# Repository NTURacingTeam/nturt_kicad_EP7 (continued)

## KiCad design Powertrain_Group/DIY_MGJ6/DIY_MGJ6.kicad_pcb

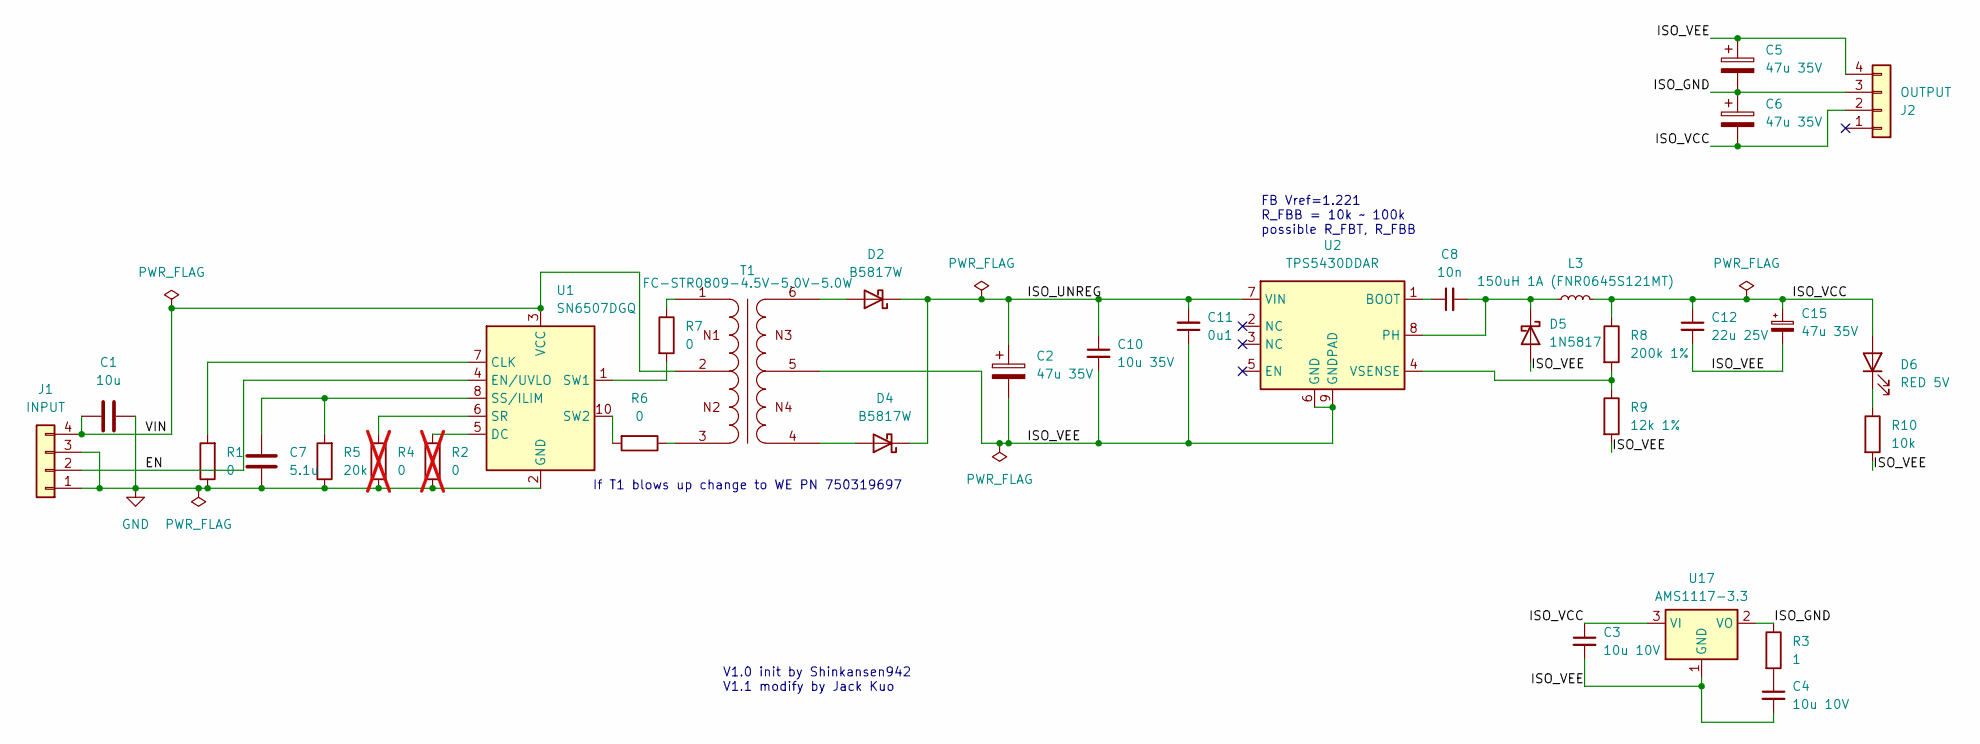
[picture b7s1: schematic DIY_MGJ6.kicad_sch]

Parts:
C1: 10u; C_1206_3216Metric
C2, C5, C6, C15: 47u 35V; CP_Elec_5x5.4
C3, C4: 10u 10V; C_1206_3216Metric
C7: 5.1u; C_0402_1005Metric
C8: 10n; C_0603_1608Metric
C10: 10u 35V; C_1206_3216Metric
C11: 0u1; C_0603_1608Metric
C12: 22u 25V; C_1206_3216Metric
D2, D4: B5817W; D_SOD-123
D5: 1N5817; D_SOD-123
D6: RED 5V; LED_0603_1608Metric
J1: INPUT; PinHeader_2x02_P2.54mm_Horizontal
J2: OUTPUT; PinHeader_2x02_P2.54mm_Horizontal
L3: 150uH 1A (FNR0645S121MT); L_APV_ANR6045
R1: 0; R_0402_1005Metric
R2, R4: 0; R_0402_1005Metric; not fitted
R3: 1; R_1206_3216Metric
R5: 20k; R_0402_1005Metric
R6, R7: 0; R_0805_2012Metric
R8: 200k 1%; R_0603_1608Metric
R9: 12k 1%; R_0603_1608Metric
R10: 10k; R_0603_1608Metric
T1: FC-STR0809-4.5V-5.0V-5.0W; T_Wurth_WE-PPTI-1308; Part Number 750319697
U1: SN6507DGQ; HVSSOP-10-1EP_3x3mm_P0.5mm_EP1.57x1.88mm
U2: TPS5430DDAR; TI_SO-PowerPAD-8_ThermalVias
U17: AMS1117-3.3; SOT-223-3_TabPin2

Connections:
/EN: J1.2, U1.4 (EN/UVLO)
/ISO_GND: C5.2, C6.1, J2.3, R3.1, U17.2 (VO)
/ISO_UNREG: C2.1, C10.1, C11.2, D2.1 (K), D4.1 (K), U2.7 (VIN)
/ISO_VCC: C3.1, C6.2, C12.1, C15.1, D6.2 (A), J2.2, L3.2, R8.1, U17.3 (VI)
/ISO_VEE: C2.2, C3.2, C4.2, C5.1, C10.2, C11.1, C12.2, C15.2, D5.2 (A), J2.4, R9.2, R10.2, T1.5, U2.6 (GND), U2.9 (GNDPAD), U17.1 (GND)
/VIN: C1.1, J1.4, T1.2, U1.3 (VCC)
GND: C1.2, C7.1, J1.1, J1.3, R1.1, R2.1, R4.1, R5.1, U1.2 (GND), U1.9 (GND), U1.11 (GND)
unnamed: C4.1, R3.2
unnamed: D2.2 (A), T1.6
unnamed: D4.2 (A), T1.4
unnamed: C8.2, D5.1 (K), L3.1, U2.8 (PH)
unnamed: D6.1 (K), R10.1
unnamed: R6.1, T1.3
unnamed: R7.1, T1.1
unnamed: R1.2, U1.7 (CLK)
unnamed: R2.2, U1.5 (DC)
unnamed: R4.2, U1.6 (SR)
unnamed: C7.2, R5.2, U1.8 (SS/ILIM)
unnamed: R7.2, U1.1 (SW1)
unnamed: R6.2, U1.10 (SW2)
unnamed: C8.1, U2.1 (BOOT)
unnamed: R8.2, R9.1, U2.4 (VSENSE)

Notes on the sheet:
FB Vref=1.221 R_FBB = 10k ~ 100k possible R_FBT, R_FBB
V1.0 init by Shinkansen942 V1.1 modify by Jack Kuo
If T1 blows up change to WE PN 750319697

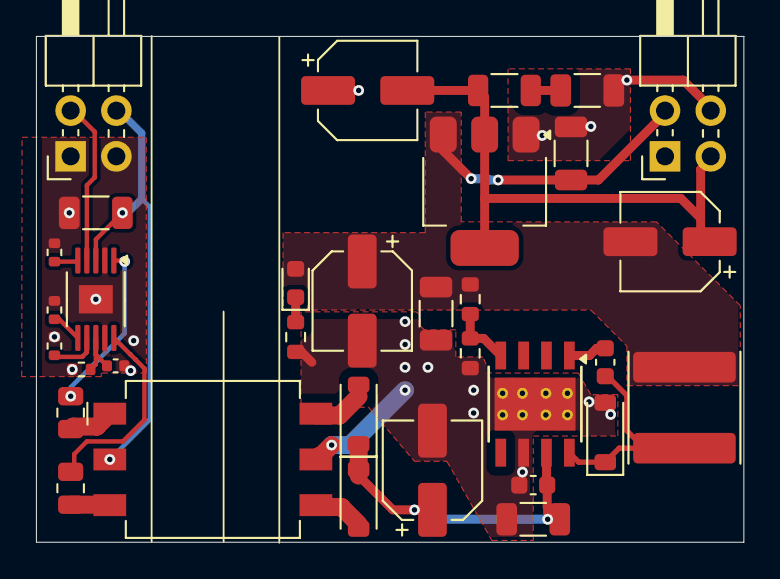
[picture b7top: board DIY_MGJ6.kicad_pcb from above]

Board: 2 copper layers, 39.3 x 28.1 mm, 33 parts (0 on the bottom side), 22 nets.

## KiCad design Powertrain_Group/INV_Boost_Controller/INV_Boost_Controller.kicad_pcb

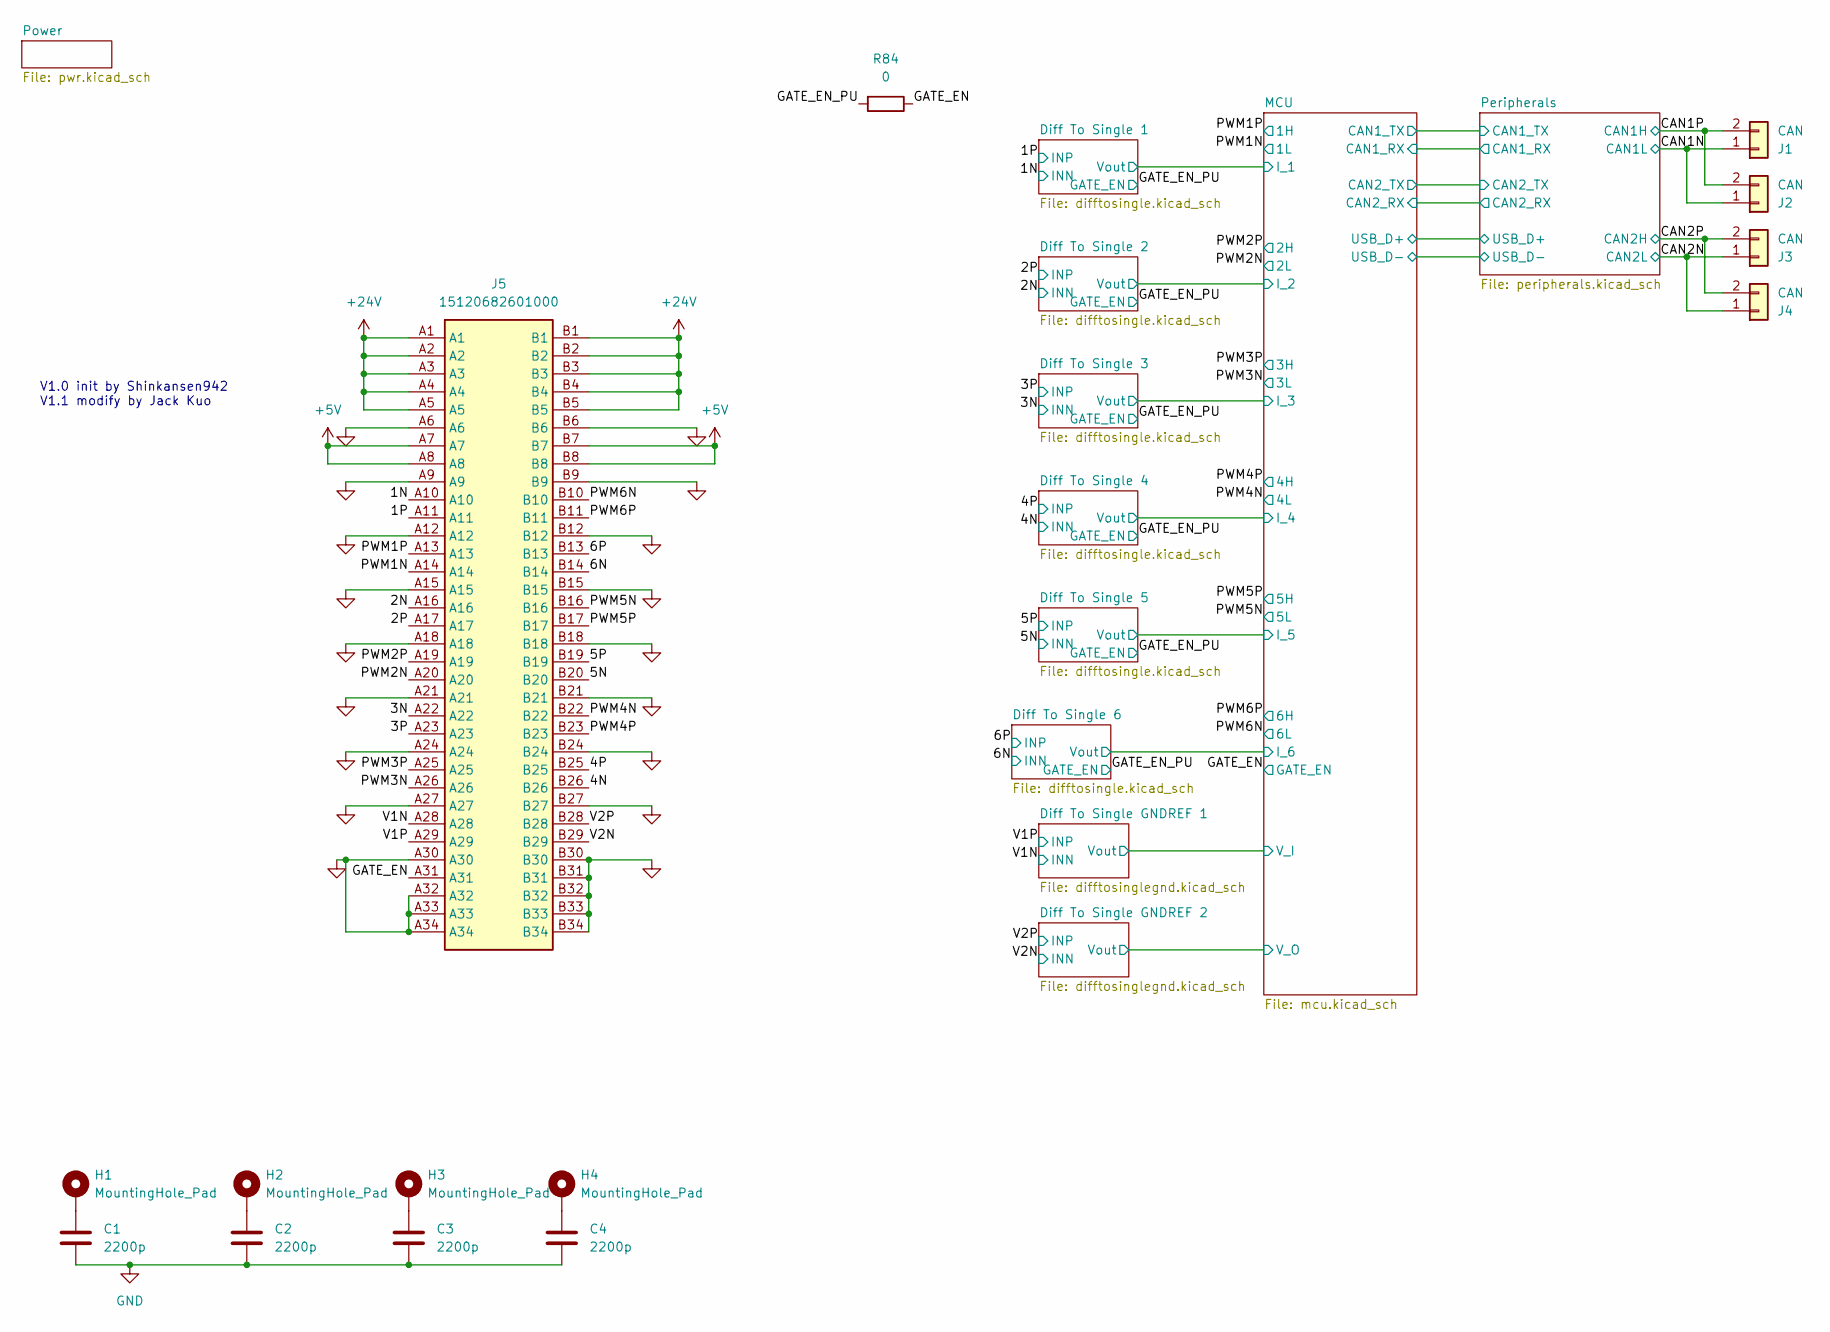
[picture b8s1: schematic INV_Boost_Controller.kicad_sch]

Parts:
C1, C2, C3, C4: 2200p; C_8060_Murata_DK1
H1, H2, H3, H4: MountingHole_Pad; MountingHole_4.3mm_M4_Pad_Via
J1, J2, J3, J4: CAN; JST_XH_B2B-XH-A_1x02_P2.50mm_Vertical
J5: 15120682601000; Harting 15120682601000; Manufacturer_Part_Number 15120682601000; Mouser Part Number 617-15120682601000
R84: 0; R_0402_1005Metric

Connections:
+5V: J5.A7, J5.A8, J5.B7, J5.B8; also elsewhere on the board
+24V: J5.A1, J5.A2, J5.A3, J5.A4, J5.A5, J5.B1, J5.B2, J5.B3, J5.B4, J5.B5; also elsewhere on the board
/1N: J5.A10; also elsewhere on the board
/1P: J5.A11; also elsewhere on the board
/2N: J5.A16; also elsewhere on the board
/2P: J5.A17; also elsewhere on the board
/3N: J5.A22; also elsewhere on the board
/3P: J5.A23; also elsewhere on the board
/4N: J5.B26; also elsewhere on the board
/4P: J5.B25; also elsewhere on the board
/5N: J5.B20; also elsewhere on the board
/5P: J5.B19; also elsewhere on the board
/6N: J5.B14; also elsewhere on the board
/6P: J5.B13; also elsewhere on the board
/CAN1N: J1.1, J2.1; also elsewhere on the board
/CAN1P: J1.2, J2.2; also elsewhere on the board
/CAN2N: J3.1, J4.1; also elsewhere on the board
/CAN2P: J3.2, J4.2; also elsewhere on the board
/GATE_EN: J5.A31, R84.1; also elsewhere on the board
/GATE_EN_PU: R84.2; also elsewhere on the board
/PWM1N: J5.A14; also elsewhere on the board
/PWM1P: J5.A13; also elsewhere on the board
/PWM2N: J5.A20; also elsewhere on the board
/PWM2P: J5.A19; also elsewhere on the board
/PWM3N: J5.A26; also elsewhere on the board
/PWM3P: J5.A25; also elsewhere on the board
/PWM4N: J5.B22; also elsewhere on the board
/PWM4P: J5.B23; also elsewhere on the board
/PWM5N: J5.B16; also elsewhere on the board
/PWM5P: J5.B17; also elsewhere on the board
/PWM6N: J5.B10; also elsewhere on the board
/PWM6P: J5.B11; also elsewhere on the board
/V1N: J5.A28; also elsewhere on the board
/V1P: J5.A29; also elsewhere on the board
/V2N: J5.B29; also elsewhere on the board
/V2P: J5.B28; also elsewhere on the board
GND: C1.1, C2.1, C3.1, C4.1, J5.A6, J5.A9, J5.A12, J5.A15, J5.A18, J5.A21, J5.A24, J5.A27, J5.A30, J5.A32, J5.A33, J5.A34, J5.B6, J5.B9, J5.B12, J5.B15, J5.B18, J5.B21, J5.B24, J5.B27, J5.B30, J5.B31, J5.B32, J5.B33, J5.B34; also elsewhere on the board
unnamed: C1.2, H1.1
unnamed: C2.2, H2.1
unnamed: C3.2, H3.1
unnamed: C4.2, H4.1

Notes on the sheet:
V1.0 init by Shinkansen942 V1.1 modify by Jack Kuo

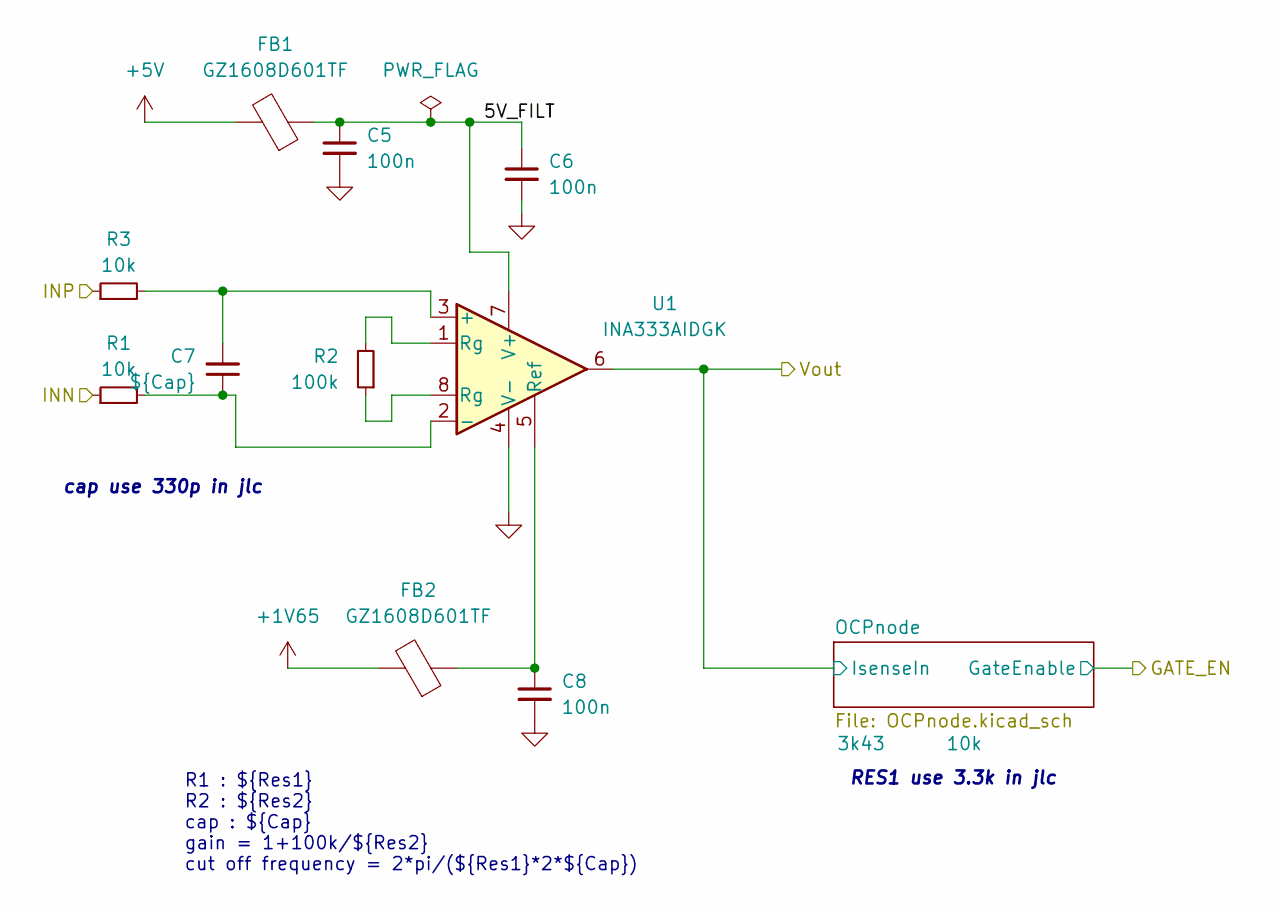
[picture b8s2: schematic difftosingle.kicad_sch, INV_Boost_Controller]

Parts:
C5, C6, C8: 100n; C_0402_1005Metric
C7: ${Cap}; C_0402_1005Metric
FB1, FB2: GZ1608D601TF; C_0603_1608Metric
R1, R3: 10k; R_0402_1005Metric
R2: 100k; R_0402_1005Metric
U1: INA333AIDGK; VSSOP-8_3x3mm_P0.65mm

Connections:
+1V65: FB2.2; also elsewhere on the board
+5V: FB1.2; also elsewhere on the board
/2N: R1.1; also elsewhere on the board
/2P: R3.1; also elsewhere on the board
/Diff To Single 2/5V_FILT: C5.1, C6.1, FB1.1, U1.7 (V+)
/Diff To Single 2/Vout: U1.6; also elsewhere on the board
GND: C5.2, C6.2, C8.2, U1.4 (V-); also elsewhere on the board
unnamed: R2.1, U1.8 (Rg)
unnamed: R2.2, U1.1 (Rg)
unnamed: C7.2, R3.2, U1.3 (+)
unnamed: C7.1, R1.2, U1.2 (-)
unnamed: C8.1, FB2.1, U1.5 (Ref)

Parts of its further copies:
C9, C10, C12, C13, C14, C16, C17, C18, C20, C21, C22, C24, C77, C78, C80: 100n; C_0402_1005Metric
FB3, FB4, FB5, FB6, FB7, FB8, FB9, FB10, FB16, FB17: GZ1608D601TF; C_0603_1608Metric
R4, R6, R7, R9, R10, R12, R13, R15, R62, R64: 10k; R_0402_1005Metric
R5, R8, R11, R14, R63: 100k; R_0402_1005Metric
U2, U3, U4, U5, U16: INA333AIDGK; VSSOP-8_3x3mm_P0.65mm

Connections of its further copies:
+1V65: FB4.2, FB6.2, FB8.2, FB10.2, FB17.2; also elsewhere on the board
+5V: FB3.2, FB5.2, FB7.2, FB9.2, FB16.2; also elsewhere on the board
/1N: R62.1; also elsewhere on the board
/1P: R64.1; also elsewhere on the board
/3N: R4.1; also elsewhere on the board
/3P: R6.1; also elsewhere on the board
/4N: R7.1; also elsewhere on the board
/4P: R9.1; also elsewhere on the board
/5N: R10.1; also elsewhere on the board
/5P: R12.1; also elsewhere on the board
/6N: R13.1; also elsewhere on the board
/6P: R15.1; also elsewhere on the board
/Diff To Single 1/5V_FILT: C77.1, C78.1, FB16.1, U16.7 (V+)
/Diff To Single 1/Vout: U16.6; also elsewhere on the board
/Diff To Single 3/5V_FILT: C9.1, C10.1, FB3.1, U2.7 (V+)
/Diff To Single 3/Vout: U2.6; also elsewhere on the board
/Diff To Single 4/5V_FILT: C13.1, C14.1, FB5.1, U3.7 (V+)
/Diff To Single 4/Vout: U3.6; also elsewhere on the board
/Diff To Single 5/5V_FILT: C17.1, C18.1, FB7.1, U4.7 (V+)
/Diff To Single 5/Vout: U4.6; also elsewhere on the board
/Diff To Single 6/5V_FILT: C21.1, C22.1, FB9.1, U5.7 (V+)
/Diff To Single 6/Vout: U5.6; also elsewhere on the board
GND: C9.2, C10.2, C12.2, C13.2, C14.2, C16.2, C17.2, C18.2, C20.2, C21.2, C22.2, C24.2, C77.2, C78.2, C80.2, U2.4 (V-), U3.4 (V-), U4.4 (V-), U5.4 (V-), U16.4 (V-); also elsewhere on the board
unnamed: R5.1, U2.8 (Rg)
unnamed: R5.2, U2.1 (Rg)
unnamed: R8.1, U3.8 (Rg)
unnamed: R8.2, U3.1 (Rg)
unnamed: R11.1, U4.8 (Rg)
unnamed: R11.2, U4.1 (Rg)
unnamed: R14.1, U5.8 (Rg)
unnamed: R14.2, U5.1 (Rg)
unnamed: R63.1, U16.8 (Rg)
unnamed: R63.2, U16.1 (Rg)
unnamed 143: R6.2, U2.3 (+); also elsewhere on the board
unnamed 144: R4.2, U2.2 (-); also elsewhere on the board
unnamed: C12.1, FB4.1, U2.5 (Ref)
unnamed 146: R9.2, U3.3 (+); also elsewhere on the board
unnamed 147: R7.2, U3.2 (-); also elsewhere on the board
unnamed: C16.1, FB6.1, U3.5 (Ref)
unnamed 149: R12.2, U4.3 (+); also elsewhere on the board
unnamed 150: R10.2, U4.2 (-); also elsewhere on the board
unnamed: C20.1, FB8.1, U4.5 (Ref)
unnamed 152: R15.2, U5.3 (+); also elsewhere on the board
unnamed 153: R13.2, U5.2 (-); also elsewhere on the board
unnamed: C24.1, FB10.1, U5.5 (Ref)
unnamed 170: R64.2, U16.3 (+); also elsewhere on the board
unnamed 171: R62.2, U16.2 (-); also elsewhere on the board
unnamed: C80.1, FB17.1, U16.5 (Ref)

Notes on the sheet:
R1 : ${Res1} R2 : ${Res2} cap : ${Cap} gain = 1+100k/${Res2} cut off frequency = 2*pi/(${Res1}*2*${Cap})
cap use 330p in jlc
RES1 use 3.3k in jlc

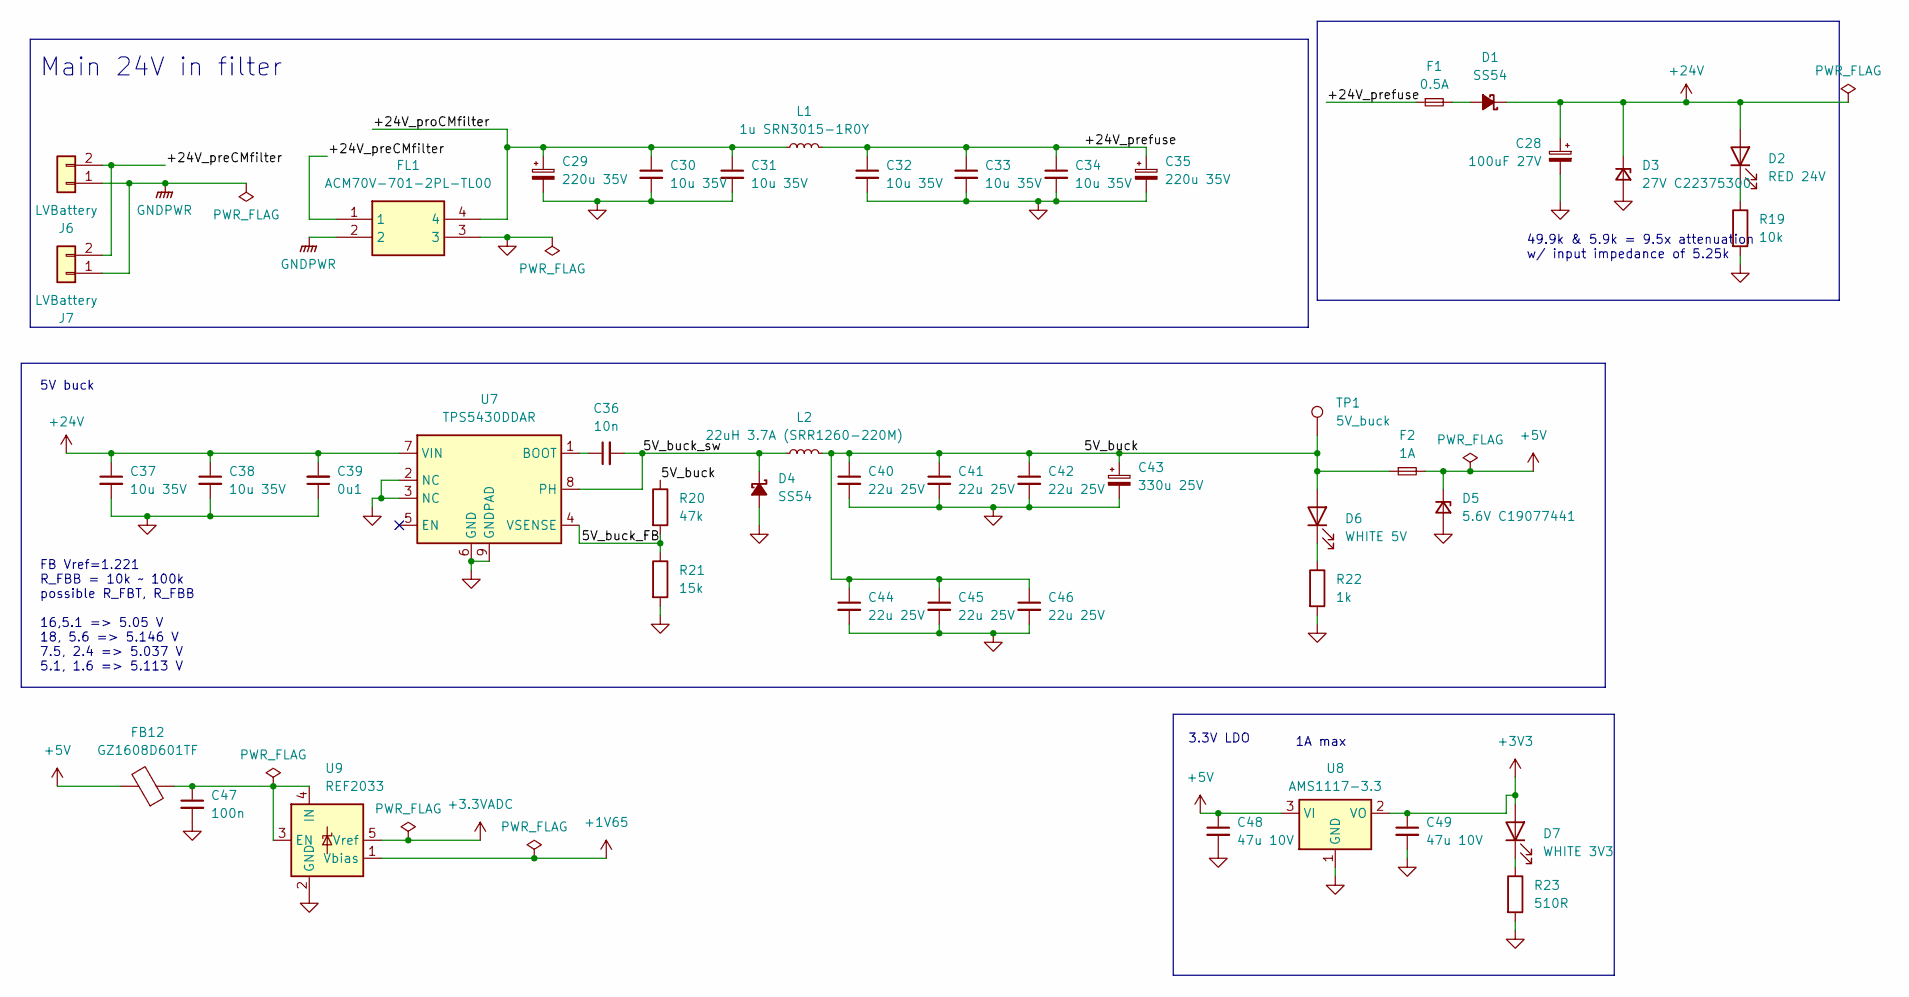
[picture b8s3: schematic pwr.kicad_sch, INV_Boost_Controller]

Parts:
C28: 100uF 27V; CP_Radial_D10.0mm_P5.00mm
C29, C35: 220u 35V; CP_Radial_D8.0mm_P3.80mm
C30, C31, C32, C33, C34, C37, C38: 10u 35V; C_1206_3216Metric
C36: 10n; C_0603_1608Metric
C39: 0u1; C_0603_1608Metric
C40, C41, C42, C44, C45, C46: 22u 25V; C_1206_3216Metric
C43: 330u 25V; CP_Radial_D8.0mm_P3.80mm
C47: 100n; C_0402_1005Metric
C48, C49: 47u 10V; C_1206_3216Metric
D1, D4: SS54; D_SMA
D2: RED 24V; LED_0603_1608Metric
D3: 27V C22375300; D_SOD-323
D5: 5.6V C19077441; D_SOD-323
D6: WHITE 5V; LED_0603_1608Metric
D7: WHITE 3V3; LED_0603_1608Metric
F1: 0.5A; Fuse_1206_3216Metric
F2: 1A; Fuse_1206_3216Metric
FB12: GZ1608D601TF; C_0603_1608Metric
FL1: ACM70V-701-2PL-TL00; Common_Mode_Choke_4A_ACM70V7012PLTL00; Mouser Part Number 810-ACM70V7012PLTL00
J6, J7: LVBattery; JST_VH_B2P-VH_1x02_P3.96mm_Vertical
L1: 1u SRN3015-1R0Y; L_Wuerth_MAPI-3015
L2: 22uH 3.7A (SRR1260-220M); L_Bourns_SRR1260
R19: 10k; R_0402_1005Metric
R20: 47k; R_0603_1608Metric
R21: 15k; R_0603_1608Metric
R22: 1k; R_0402_1005Metric
R23: 510R; R_0402_1005Metric
TP1: 5V_buck; TestPoint_Pad_D1.0mm
U7: TPS5430DDAR; TI_SO-PowerPAD-8_ThermalVias
U8: AMS1117-3.3; SOT-223-3_TabPin2
U9: REF2033; SOT-23-5

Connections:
+1V65: U9.1 (Vbias); also elsewhere on the board
+3.3VADC: U9.5 (Vref); also elsewhere on the board
+3V3: C49.1, D7.2 (A), U8.2 (VO); also elsewhere on the board
+5V: C48.1, D5.1 (K), F2.2, FB12.2, U8.3 (VI); also elsewhere on the board
+24V: C28.1, C37.1, C38.1, C39.2, D1.1 (K), D2.2 (A), D3.1 (K), U7.7 (VIN); also elsewhere on the board
/Power/5V_buck: C40.1, C41.1, C42.1, C43.1, C44.1, C45.1, C46.1, D6.2 (A), F2.1, L2.2, R20.1, TP1.1
/Power/5V_buck_FB: R20.2, R21.1, U7.4 (VSENSE)
/Power/5V_buck_sw: C36.2, D4.1 (K), L2.1, U7.8 (PH)
/Power/+24V_preCMfilter: FL1.1, J6.2, J7.2
/Power/+24V_prefuse: C32.1, C33.1, C34.1, C35.1, F1.1, L1.2
/Power/+24V_proCMfilter: C29.1, C30.1, C31.1, FL1.4, L1.1
GND: C28.2, C29.2, C30.2, C31.2, C32.2, C33.2, C34.2, C35.2, C37.2, C38.2, C39.1, C40.2, C41.2, C42.2, C43.2, C44.2, C45.2, C46.2, C47.2, C48.2, C49.2, D3.2 (A), D4.2 (A), D5.2 (A), FL1.3, R19.2, R21.2, R22.2, R23.2, U7.2 (NC), U7.3 (NC), U7.6 (GND), U7.9 (GNDPAD), U8.1 (GND), U9.2 (GND); also elsewhere on the board
GNDPWR: FL1.2, J6.1, J7.1
unnamed: D1.2 (A), F1.2
unnamed: D2.1 (K), R19.1
unnamed: D6.1 (K), R22.1
unnamed: D7.1 (K), R23.1
unnamed: C36.1, U7.1 (BOOT)
unnamed: C47.1, FB12.1, U9.3 (EN), U9.4 (IN)

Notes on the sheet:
1A max
FB Vref=1.221 R_FBB = 10k ~ 100k possible R_FBT, R_FBB 16,5.1 => 5.05 V 18, 5.6 => 5.146 V 7.5, 2.4 => 5.037 V 5.1, 1.6 => 5.113 V
Main 24V in filter
49.9k & 5.9k = 9.5x attenuation w/ input impedance of 5.25k
5V buck
3.3V LDO

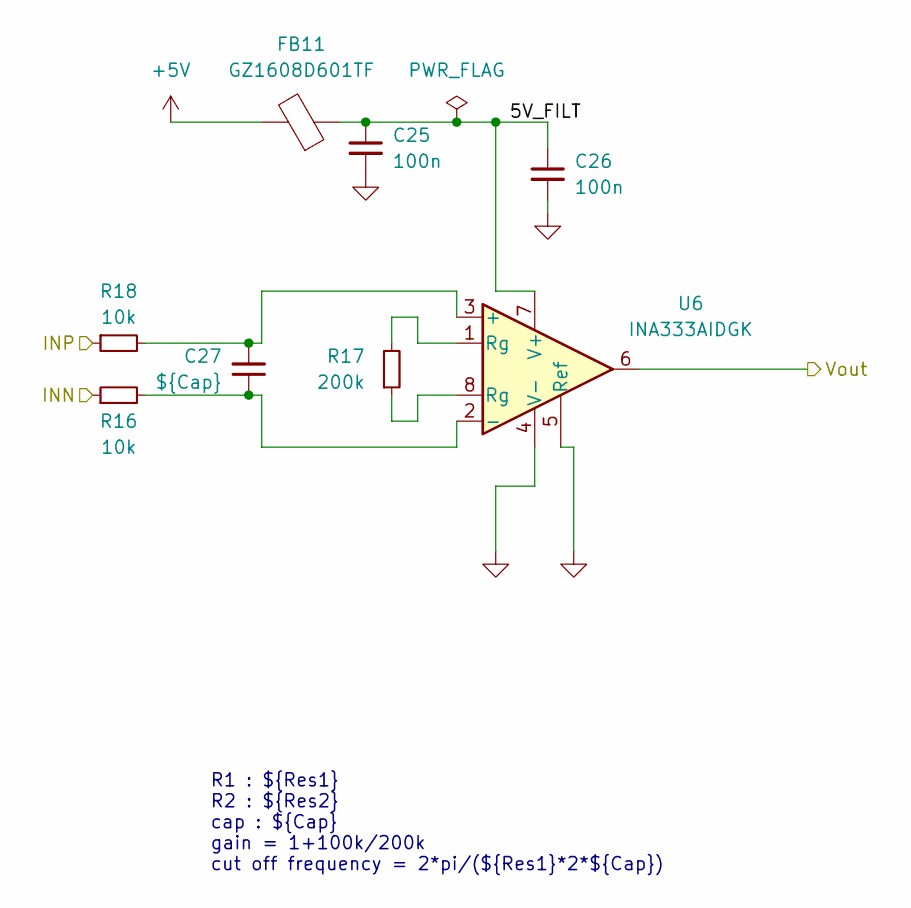
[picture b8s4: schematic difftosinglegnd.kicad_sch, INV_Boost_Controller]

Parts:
C25, C26: 100n; C_0402_1005Metric
C27: ${Cap}; C_0402_1005Metric
FB11: GZ1608D601TF; C_0603_1608Metric
R16, R18: 10k; R_0402_1005Metric
R17: 200k; R_0402_1005Metric
U6: INA333AIDGK; VSSOP-8_3x3mm_P0.65mm

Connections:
+5V: FB11.2; also elsewhere on the board
/Diff To Single GNDREF 1/5V_FILT: C25.1, C26.1, FB11.1, U6.7 (V+)
/Diff To Single GNDREF 1/Vout: U6.6; also elsewhere on the board
/V1N: R16.1; also elsewhere on the board
/V1P: R18.1; also elsewhere on the board
GND: C25.2, C26.2, U6.4 (V-), U6.5 (Ref); also elsewhere on the board
unnamed: R17.1, U6.8 (Rg)
unnamed: R17.2, U6.1 (Rg)
unnamed: C27.2, R18.2, U6.3 (+)
unnamed: C27.1, R16.2, U6.2 (-)

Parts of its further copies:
C81, C82: 100n; C_0402_1005Metric
FB18: GZ1608D601TF; C_0603_1608Metric
R65, R67: 10k; R_0402_1005Metric
R66: 200k; R_0402_1005Metric
U17: INA333AIDGK; VSSOP-8_3x3mm_P0.65mm

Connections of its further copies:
+5V: FB18.2; also elsewhere on the board
/Diff To Single GNDREF 2/5V_FILT: C81.1, C82.1, FB18.1, U17.7 (V+)
/Diff To Single GNDREF 2/Vout: U17.6; also elsewhere on the board
/V2N: R65.1; also elsewhere on the board
/V2P: R67.1; also elsewhere on the board
GND: C81.2, C82.2, U17.4 (V-), U17.5 (Ref); also elsewhere on the board
unnamed: R66.1, U17.8 (Rg)
unnamed: R66.2, U17.1 (Rg)
unnamed 173: R67.2, U17.3 (+); also elsewhere on the board
unnamed 174: R65.2, U17.2 (-); also elsewhere on the board

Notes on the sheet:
R1 : ${Res1} R2 : ${Res2} cap : ${Cap} gain = 1+100k/200k cut off frequency = 2*pi/(${Res1}*2*${Cap})

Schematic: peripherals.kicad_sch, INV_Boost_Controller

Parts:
C50, C55: 4u7 10v; C_0402_1005Metric
C51, C52, C56, C57: 0u1; C_0402_1005Metric
C53, C54, C58, C59: 22p; C_0402_1005Metric
D8, D9: NUP2105L; SOT-23
FL2, FL3: EXC-X4CE900U; EXCX4CE900U; Mouser Part Number 667-EXC-X4CE900U
J8: USB_C_Receptacle_USB2.0_16P; USB_C_Receptacle_G-Switch_GT-USB-7051x
R24, R25, R28, R29: 22R; R_0402_1005Metric
R26, R30: 90R; R_0402_1005Metric; not fitted
R27, R31: 10k; R_0402_1005Metric
R32, R33: 5.1k; R_0402_1005Metric
SW1: SW_DIP_x01; SW_DIP_SPSTx01_Slide_9.78x4.72mm_W7.62mm_P2.54mm
U10, U11: TCAN1042VDRQ1; SOIC-8_3.9x4.9mm_P1.27mm
U12: SRV05-4; SOT-23-6

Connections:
+3V3: C52.1, C57.1, U10.5 (VIO), U11.5 (VIO); also elsewhere on the board
+5V: C50.1, C51.1, C55.1, C56.1, SW1.1, U10.3 (VCC), U11.3 (VCC); also elsewhere on the board
/CAN1N: C58.1, D9.1 (K), FL3.3, R30.2; also elsewhere on the board
/CAN1P: C59.1, D9.2 (K), FL3.4, R30.1; also elsewhere on the board
/CAN2N: C53.1, D8.1 (K), FL2.3, R26.2; also elsewhere on the board
/CAN2P: C54.1, D8.2 (K), FL2.4, R26.1; also elsewhere on the board
/MCU/CAN1_RX: R29.1; also elsewhere on the board
/MCU/CAN1_TX: R28.1; also elsewhere on the board
/MCU/CAN2_RX: R25.1; also elsewhere on the board
/MCU/CAN2_TX: R24.1; also elsewhere on the board
/Peripherals/D+: J8.A6 (D+), J8.B6 (D+), U12.3 (IO2), U12.4 (IO3); also elsewhere on the board
/Peripherals/D-: J8.A7 (D-), J8.B7 (D-), U12.1 (IO1), U12.6 (IO4); also elsewhere on the board
/Peripherals/PRE_CAN1N: FL3.2, U11.6 (CANL)
/Peripherals/PRE_CAN1P: FL3.1, U11.7 (CANH)
/Peripherals/PRE_CAN2N: FL2.2, U10.6 (CANL)
/Peripherals/PRE_CAN2P: FL2.1, U10.7 (CANH)
/Peripherals/VBUS: J8.A4 (VBUS), J8.A9 (VBUS), J8.B4 (VBUS), J8.B9 (VBUS), SW1.2, U12.5 (VP)
GND: C50.2, C51.2, C52.2, C53.2, C54.2, C55.2, C56.2, C57.2, C58.2, C59.2, D8.3 (A), D9.3 (A), J8.A1 (GND), J8.A12 (GND), J8.B1 (GND), J8.B12 (GND), J8.S1 (SHIELD), R27.2, R31.2, R32.2, R33.2, U10.2 (GND), U11.2 (GND), U12.2 (VN); also elsewhere on the board
unnamed: J8.A5 (CC1), R32.1
unnamed: J8.B5 (CC2), R33.1
unnamed: R25.2, U10.4 (RXD)
unnamed: R27.1, U10.8 (STB)
unnamed: R24.2, U10.1 (TXD)
unnamed: R29.2, U11.4 (RXD)
unnamed: R31.1, U11.8 (STB)
unnamed: R28.2, U11.1 (TXD)

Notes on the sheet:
CAN1
cap reference: https://www.nxp.com/docs/en/supporting-information/AH1014_v1_4_Application_Hints_TJA1042_43_48_51.pdf
CAN2
we use 1M => about 50pF to ground for both H and L but 30pF already persist in NUP2105 => only 22pF added additionaly but additionaly, TCAN1042 itself has 24pF to GND and 12pF H to L.
USB

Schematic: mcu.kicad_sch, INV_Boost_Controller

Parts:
C60, C61, C62, C63, C64: 100n; C_0402_1005Metric
C65, C66: 4u7; C_0402_1005Metric
C67, C70, C71, C73: 0u1; C_0402_1005Metric
C68, C69: 10u 6V; C_0402_1005Metric
C72, C74: 27p; C_0402_1005Metric
D10, D14: R LED; LED_0603_1608Metric
D11, D15: Y LED; LED_0603_1608Metric
D12, D16: G LED; LED_0603_1608Metric
D13, D17: B LED; LED_0603_1608Metric
FB13: GZ1608D601TF; C_0603_1608Metric
J9: STDC14; box_header_14P_pitch1.27
J10, J11, J12, J13: TEMP; JST_XA_B02B-XASK-1_1x02_P2.50mm_Vertical
J14: MSD-4-A; MSD4A; Mouser Part Number 179-MSD-4-A
R34, R35, R36, R37, R38, R39, R40: 10k; R_0402_1005Metric
R41: 100R; R_0402_1005Metric
R42, R43, R44, R45, R46, R47, R48, R49: 2k2; R_0402_1005Metric
R50, R51, R52, R53: 4k7; R_0402_1005Metric
SW2, SW3: TS-1187A-B-A-B; SW_SPST_TL3342
U13: STM32G474VETx; LQFP-100_14x14mm_P0.5mm
Y1: X322516MLB4SI (16MHz); Crystal_SMD_3225-4Pin_3.2x2.5mm

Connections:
+3.3VADC: C69.1, FB13.2, R36.1, R37.1, R38.1, R39.1; also elsewhere on the board
+3V3: C60.1, C61.1, C62.1, C63.1, C64.1, C65.1, C66.1, J9.3, J14.4 (VDD), R34.1, R50.2, R51.2, R52.2, R53.2, SW3.1, U13.6 (VBAT), U13.24 (VDD), U13.49 (VDD), U13.64 (VDD), U13.75 (VDD), U13.100 (VDD); also elsewhere on the board
/Diff To Single 1/Vout: U13.21 (PA1); also elsewhere on the board
/Diff To Single 2/Vout: U13.22 (PA2); also elsewhere on the board
/Diff To Single 3/Vout: U13.25 (PA3); also elsewhere on the board
/Diff To Single 4/Vout: U13.26 (PA4); also elsewhere on the board
/Diff To Single 5/Vout: U13.27 (PA5); also elsewhere on the board
/Diff To Single 6/Vout: U13.28 (PA6); also elsewhere on the board
/Diff To Single GNDREF 1/Vout: U13.32 (PB0); also elsewhere on the board
/Diff To Single GNDREF 2/Vout: U13.33 (PB1); also elsewhere on the board
/GATE_EN: R40.2; also elsewhere on the board
/MCU/BOOT0: C73.1, R35.2, SW3.2, U13.95 (PB8)
/MCU/CAN1_RX: U13.82 (PD0); also elsewhere on the board
/MCU/CAN1_TX: U13.83 (PD1); also elsewhere on the board
/MCU/CAN2_RX: U13.92 (PB5); also elsewhere on the board
/MCU/CAN2_TX: U13.93 (PB6); also elsewhere on the board
/MCU/LED_B12: R42.1, U13.51 (PB12)
/MCU/LED_B13: R43.1, U13.52 (PB13)
/MCU/LED_B14: R44.1, U13.53 (PB14)
/MCU/LED_B15: R45.1, U13.54 (PB15)
/MCU/LED_D8: R46.1, U13.55 (PD8)
/MCU/LED_D9: R47.1, U13.56 (PD9)
/MCU/LED_D10: R48.1, U13.57 (PD10)
/MCU/LED_D11: R49.1, U13.58 (PD11)
/MCU/NRST: C70.1, C71.1, J9.12, R34.2, SW2.2, U13.14 (PG10)
/MCU/OSC_IN: C72.1, U13.12 (PF0), Y1.3
/MCU/OSC_OUT: C74.1, U13.13 (PF1), Y1.1
/MCU/SD_SPI_CLK: J14.5 (CLK), R52.1, U13.79 (PC10)
/MCU/SD_SPI_CS: J14.2 (CD/DAT3), R50.1, U13.78 (PA15)
/MCU/SD_SPI_MISO: J14.7 (DAT0), R53.1, U13.80 (PC11)
/MCU/SD_SPI_MOSI: J14.3 (CMD), R51.1, U13.81 (PC12)
/MCU/TEMP_1: J10.2, R36.2, U13.43 (PE12)
/MCU/TEMP_2: J11.2, R37.2, U13.44 (PE13)
/MCU/TEMP_3: J12.2, R38.2, U13.45 (PE14)
/MCU/TEMP_4: J13.2, R39.2, U13.46 (PE15)
/MCU/T_CLK: J9.6, U13.77 (PA14)
/MCU/T_DIO: J9.4, U13.76 (PA13)
/MCU/USART1_RX: J9.13, U13.71 (PA10)
/MCU/USART1_TX: J9.14, U13.70 (PA9)
/MCU/VDDA_MCU: C67.1, C68.1, FB13.1, U13.36 (VREF+), U13.37 (VDDA)
/PWM1N: U13.39 (PE8); also elsewhere on the board
/PWM1P: U13.40 (PE9); also elsewhere on the board
/PWM2N: U13.4 (PE5); also elsewhere on the board
/PWM2P: U13.2 (PE3); also elsewhere on the board
/PWM3N: U13.90 (PB3); also elsewhere on the board
/PWM3P: U13.65 (PC6); also elsewhere on the board
/PWM4N: U13.41 (PE10); also elsewhere on the board
/PWM4P: U13.42 (PE11); also elsewhere on the board
/PWM5N: U13.3 (PE4); also elsewhere on the board
/PWM5P: U13.1 (PE2); also elsewhere on the board
/PWM6N: U13.91 (PB4); also elsewhere on the board
/PWM6P: U13.66 (PC7); also elsewhere on the board
/Peripherals/D+: U13.73 (PA12); also elsewhere on the board
/Peripherals/D-: U13.72 (PA11); also elsewhere on the board
GND: C60.2, C61.2, C62.2, C63.2, C64.2, C65.2, C66.2, C67.2, C68.2, C69.2, C70.2, C71.2, C72.2, C73.2, C74.2, D10.1 (K), D11.1 (K), D12.1 (K), D13.1 (K), D14.1 (K), D15.1 (K), D16.1 (K), D17.1 (K), J9.5, J9.7, J10.1, J11.1, J12.1, J13.1, J14.6 (VSS), J14.G1 (GND_1), J14.G2 (GND_2), J14.G3 (GND_3), J14.G4 (GND_4), R35.1, R41.1, SW2.1, U13.23 (VSS), U13.35 (VSSA), U13.48 (VSS), U13.63 (VSS), U13.74 (VSS), U13.99 (VSS), Y1.2, Y1.4; also elsewhere on the board
unnamed: D10.2 (A), R42.2
unnamed: D11.2 (A), R43.2
unnamed: D12.2 (A), R44.2
unnamed: D13.2 (A), R45.2
unnamed: D14.2 (A), R46.2
unnamed: D15.2 (A), R47.2
unnamed: D16.2 (A), R48.2
unnamed: D17.2 (A), R49.2
unnamed: J9.11, R41.2
unnamed: R40.1, U13.30 (PC4)

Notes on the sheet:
T_TX
load capacitance : 15pF
STDC14 to stlink
SWO
T_RX
reference: 32F746GDISCOVERY
SDMMC

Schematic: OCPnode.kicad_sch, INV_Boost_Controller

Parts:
C75: 100n; C_0402_1005Metric
FB14: GZ1608D601TF; C_0603_1608Metric
R54, R57: ${Res1}; R_0402_1005Metric
R55, R56: ${Res2}; R_0402_1005Metric
U14: LM393; VSSOP-8_3x3mm_P0.65mm

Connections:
+3V3: FB14.1; also elsewhere on the board
/Diff To Single 2/OCPnode/filt3V3: C75.1, FB14.2, R54.1, R56.1, U14.8 (V+)
/Diff To Single 2/Vout: U14.2 (-), U14.5 (+); also elsewhere on the board
/GATE_EN_PU: U14.1, U14.7; also elsewhere on the board
GND: C75.2, R55.2, R57.2, U14.4 (V-); also elsewhere on the board
unnamed: R54.2, R55.1, U14.3 (+)
unnamed: R56.2, R57.1, U14.6 (-)

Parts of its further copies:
C76, C84, C85, C86, C87: 100n; C_0402_1005Metric
FB15, FB19, FB20, FB21, FB22: GZ1608D601TF; C_0603_1608Metric
U15, U18, U19, U20, U21: LM393; VSSOP-8_3x3mm_P0.65mm

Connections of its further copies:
+3V3: FB15.1, FB19.1, FB20.1, FB21.1, FB22.1; also elsewhere on the board
/Diff To Single 1/OCPnode/filt3V3: C87.1, FB22.2, U21.8 (V+); also elsewhere on the board
/Diff To Single 1/Vout: U21.2 (-), U21.5 (+); also elsewhere on the board
/Diff To Single 3/OCPnode/filt3V3: C76.1, FB15.2, U15.8 (V+); also elsewhere on the board
/Diff To Single 3/Vout: U15.2 (-), U15.5 (+); also elsewhere on the board
/Diff To Single 4/OCPnode/filt3V3: C84.1, FB19.2, U18.8 (V+); also elsewhere on the board
/Diff To Single 4/Vout: U18.2 (-), U18.5 (+); also elsewhere on the board
/Diff To Single 5/OCPnode/filt3V3: C85.1, FB20.2, U19.8 (V+); also elsewhere on the board
/Diff To Single 5/Vout: U19.2 (-), U19.5 (+); also elsewhere on the board
/Diff To Single 6/OCPnode/filt3V3: C86.1, FB21.2, U20.8 (V+); also elsewhere on the board
/Diff To Single 6/Vout: U20.2 (-), U20.5 (+); also elsewhere on the board
/GATE_EN_PU: U15.1, U15.7, U18.1, U18.7, U19.1, U19.7, U20.1, U20.7, U21.1, U21.7; also elsewhere on the board
GND: C76.2, C84.2, C85.2, C86.2, C87.2, U15.4 (V-), U18.4 (V-), U19.4 (V-), U20.4 (V-), U21.4 (V-); also elsewhere on the board
unnamed 168: U15.3 (+); also elsewhere on the board
unnamed 169: U15.6 (-); also elsewhere on the board
unnamed 175: U18.3 (+); also elsewhere on the board
unnamed 176: U18.6 (-); also elsewhere on the board
unnamed 177: U19.3 (+); also elsewhere on the board
unnamed 178: U19.6 (-); also elsewhere on the board
unnamed 179: U20.3 (+); also elsewhere on the board
unnamed 180: U20.6 (-); also elsewhere on the board
unnamed 181: U21.3 (+); also elsewhere on the board
unnamed 182: U21.6 (-); also elsewhere on the board
